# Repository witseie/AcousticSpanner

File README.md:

# DIY Acoustic Spanner

## Credits
* Ermes Toninelli, Mitchell A. Cox, Graham M. Gibson, Stuart D. Brown, Matthew P. Edgar, Andrew Forbes, Miles J. Padgett 
(Andrew.Forbes@wits.ac.za; Miles.Padgett@glasgow.ac.uk)

## Acknowledgements
* University of Glasgow, Scotland, United Kingdom
* University of the Witwatersrand, Johannesburg, South Africa
* EPSRC
* Centre for doctoral training in Intelligent Sensing and Measurment

## Introduction

Waves are ubiquitous in nature and we are all familiar with them: think water waves, light waves, sound waves, and so on. Everyone is familiar with the force that waves can impart on objects placed in their path. For example, a laser pointer shining on an object exerts a force on it, albeit a very small one. As it turns out, this force is directly proportional to the power of the wave and inversely proportional to its group velocity: that is, for the same power, a slower wave can exert a bigger force than a faster wave. Therefore, in the case of light waves the force is very small, as the speed of light is a very big number. Conversely, for the much slower sound waves (sound is approximately one million times slower than light) it is possible to exert a much bigger force, for an equal power expenditure.

In addition to linear momentum, both light and sound can carry orbital angular momentum (OAM). Whereas linear momentum allows one to ‘push’ objects along the direction of propagation, OAM can be used to rotate them! This form of momentum is different from the perhaps more familiar spin angular momentum, which gives rise to the phenomenon of polarisation, and it can be visualised, in the case of light, as each photon spinning on itself. When an OAM carrying field interacts with an object, it exerts a force both along the direction of propagation and around it: like the sort of force that is required to open a door, by both turning the door knob and by pushing the door.

Another example of the difference between spin angular momentum and orbital angular momentum is the Earth and Moon. The Earth rotates about it's own axis and thus has spin angular momentum. The Moon orbits around the Earth and thus has orbital angular momentum!

OAM arises from a phase structure within the field. Accordingly, many waves are used to create a certain field and the phase differences between these waves can be engineered by introducing delays, often referred to as a phased array. For example, if the waves are in phase with each other (i.e. without delays) the field can be visualised as a series of plane waves, for which the intensity of the waves is the same all over. If however, the phases are regularly changed from 0 to 2pi (one full cycle) in an azimuthal manner (going around the direction of propagation), then the field takes the form of a spiral. This is the type of field that gives rise to OAM.

In this work we use OAM carrying sound waves to build an acoustic spanner. An acoustic spanner allows to exert orbital angular momentum (OAM) on objects, causing them to rotate. Seeing this phenomenon in action is an excellent opportunity to think about the exchange of energy between sound waves and matter, and it is hence an important pedagogical tool. However, building an acoustic spanner able to spin macroscopic objects can require relatively expensive equipment and advanced technical skills. We show how to build a free-space acoustic spanner based on a 3D-printed sound-guiding structure and common electrical components. We show a video of our free-space acoustic spanner in action, in which a styrofoam packing peanut spins in a circular motion and changes direction according to the handedness of the OAM sound (see attached video).

## How do I build one?

1. You will need to get a PCB manufactured. Gerbers are provided which you can send through to your favourite manufacturer. We use Elecrow because they are cheap, fast and do a good job.
2. Accumulate all the compoments. A Bill Of Materials (BOM) is provided as a spreadsheet. The total cost is less than $100.
3. Learn to solder if you don't already know how (YouTube?). Solder all the components, carefully, to the PCB. 
4. Check your soldering and that each component is in the right place. Also check for solder bridges that shouldn't be there.
5. Burn the provided firmware to an Arduino Due using the Arduino IDE or Visual Studio Code.
6. Plug everything together and turn it on! You need to connect a 12V, 1A (or more) power supply to the top PCB for this to work.

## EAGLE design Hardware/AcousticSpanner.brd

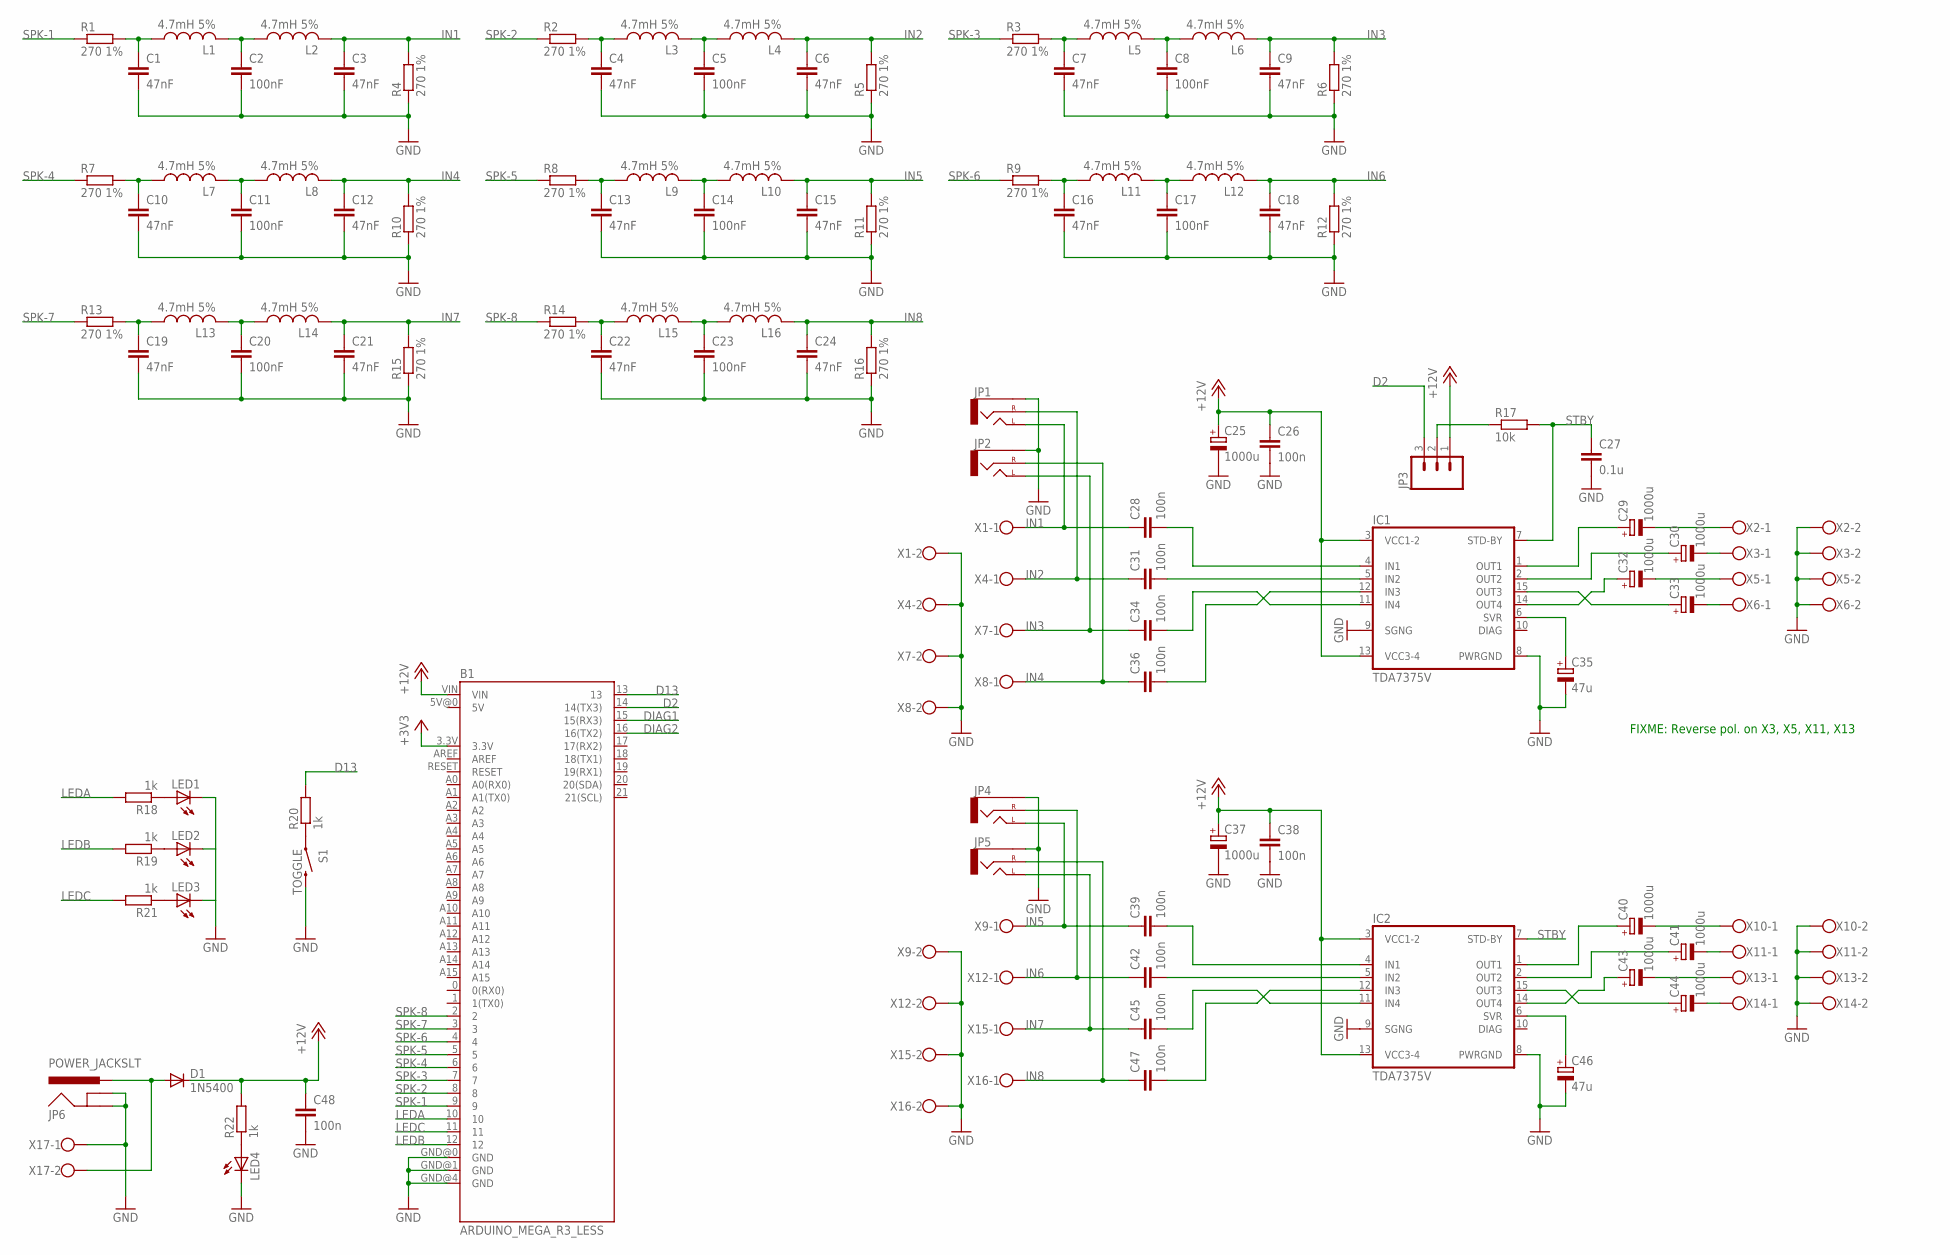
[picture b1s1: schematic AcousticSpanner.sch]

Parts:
B1: ARDUINO_MEGA_R3_LESS; ARDUINO_MEGA_LESS
C1, C3, C4, C6, C7, C9, C10, C12, C13, C15, C16, C18, C19, C21, C22, C24: 47nF; C025-025X050
C2, C5, C8, C11, C14, C17, C20, C23: 100nF; C025-025X050
C25, C29, C30, C32, C33, C37, C40, C41, C43, C44: 1000u; E5-10,5
C26, C28, C31, C34, C36, C38, C39, C42, C45, C47, C48: 100n; C025-025X050
C27: 0.1u; C025-025X050
C35, C46: 47u; E2,5-5
D1: 1N5400; DO201-15
IC1, IC2: TDA7375V; MULTIWATT-15V
JP1, JP2, JP4, JP5: AUDIO-JACKPTH; AUDIO-JACK
JP3: M03LOCK; 1X03_LOCK
JP6: POWER_JACKSLT; POWER_JACK_SLOT
L1, L2, L3, L4, L5, L6, L7, L8, L9, L10, L11, L12, L13, L14, L15, L16: 4.7mH 5%; 0207/2V
LED1, LED2, LED3, LED4: LED5MM
R1, R2, R3, R4, R5, R6, R7, R8, R9, R10, R11, R12, R13, R14, R15, R16: 270 1%; 0207/2V
R17: 10k; 0207/2V
R18, R19, R20, R21, R22: 1k; 0207/2V
S1: TOGGLE; TACTILE-PTH
X1, X2, X3, X4, X5, X6, X7, X8, X9, X10, X11, X12, X13, X14, X15, X16, X17: W237-102

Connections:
+3V3: B1.3.3V
+12V: B1.VIN, C25.+, C26.1, C37.+, C38.1, C48.1, D1.C, IC1.3 (VCC1-2), IC1.13 (VCC3-4), IC2.3 (VCC1-2), IC2.13 (VCC3-4), JP3.1, R22.2
D2: B1.14 (14(TX3)), JP3.3
D13: B1.13, R20.2
DIAG1: B1.15 (15(RX3))
DIAG2: B1.16 (16(TX2))
GND: B1.GND@0 (GND), B1.GND@1 (GND), B1.GND@4 (GND), C1.2, C2.2, C3.2, C4.2, C5.2, C6.2, C7.2, C8.2, C9.2, C10.2, C11.2, C12.2, C13.2, C14.2, C15.2, C16.2, C17.2, C18.2, C19.2, C20.2, C21.2, C22.2, C23.2, C24.2, C25.-, C26.2, C27.2, C35.-, C37.-, C38.2, C46.-, C48.2, IC1.8 (PWRGND), IC1.9 (SGNG), IC2.8 (PWRGND), IC2.9 (SGNG), JP1.SLEEVE, JP2.SLEEVE, JP4.SLEEVE, JP5.SLEEVE, JP6.GND@1 (GNDBREAK), JP6.GND@2 (GND), LED1.K (C), LED2.K (C), LED3.K (C), LED4.K (C), R4.1, R5.1, R6.1, R10.1, R11.1, R12.1, R15.1, R16.1, S1.3 (2), X1.2, X2.2, X3.2, X4.2, X5.2, X6.2, X7.2, X8.2, X9.2, X10.2, X11.2, X12.2, X13.2, X14.2, X15.2, X16.2, X17.1
IN1: C3.1, C28.1, JP1.TIP (LEFT), L2.2, R4.2, X1.1
IN2: C6.1, C31.1, JP1.RING (RIGHT), L4.2, R5.2, X4.1
IN3: C9.1, C34.1, JP2.TIP (LEFT), L6.2, R6.2, X7.1
IN4: C12.1, C36.1, JP2.RING (RIGHT), L8.2, R10.2, X8.1
IN5: C15.1, C39.1, JP4.TIP (LEFT), L10.2, R11.2, X9.1
IN6: C18.1, C42.1, JP4.RING (RIGHT), L12.2, R12.2, X12.1
IN7: C21.1, C45.1, JP5.TIP (LEFT), L14.2, R15.2, X15.1
IN8: C24.1, C47.1, JP5.RING (RIGHT), L16.2, R16.2, X16.1
LEDA: B1.10, R18.2
LEDB: B1.12, R19.2
LEDC: B1.11, R21.2
unnamed: C44.+, IC2.15 (OUT3)
unnamed: C32.+, IC1.14 (OUT4)
unnamed: C30.+, IC1.2 (OUT2)
unnamed: C29.+, IC1.1 (OUT1)
unnamed: C28.2, IC1.4 (IN1)
unnamed: C31.2, IC1.5 (IN2)
unnamed: C1.1, L1.1, R1.2
unnamed: C36.2, IC1.12 (IN3)
unnamed: C35.+, IC1.6 (SVR)
unnamed: JP3.2, R17.1
unnamed: C29.-, X2.1
unnamed: C30.-, X3.1
unnamed: C32.-, X5.1
unnamed: C33.-, X6.1
unnamed: LED4.A, R22.1
unnamed: C39.2, IC2.4 (IN1)
unnamed: C42.2, IC2.5 (IN2)
unnamed: C45.2, IC2.11 (IN4)
unnamed: C47.2, IC2.12 (IN3)
unnamed: C46.+, IC2.6 (SVR)
unnamed: C33.+, IC1.15 (OUT3)
unnamed: C43.+, IC2.14 (OUT4)
unnamed: C41.+, IC2.2 (OUT2)
unnamed: C40.+, IC2.1 (OUT1)
unnamed: C40.-, X10.1
unnamed: C41.-, X11.1
unnamed: C43.-, X13.1
unnamed: C44.-, X14.1
unnamed: LED1.A, R18.1
unnamed: LED2.A, R19.1
unnamed: R20.1, S1.1
unnamed: LED3.A, R21.1
unnamed: D1.A, JP6.PWR, X17.2
unnamed: C34.2, IC1.11 (IN4)
unnamed: C2.1, L1.2, L2.1
unnamed: C10.1, L7.1, R7.2
unnamed: C11.1, L7.2, L8.1
unnamed: C19.1, L13.1, R13.2
unnamed: C20.1, L13.2, L14.1
unnamed: C22.1, L15.1, R14.2
unnamed: C23.1, L15.2, L16.1
unnamed: C4.1, L3.1, R2.2
unnamed: C5.1, L3.2, L4.1
unnamed: C13.1, L9.1, R8.2
unnamed: C14.1, L9.2, L10.1
unnamed: C7.1, L5.1, R3.2
unnamed: C8.1, L5.2, L6.1
unnamed: C16.1, L11.1, R9.2
unnamed: C17.1, L11.2, L12.1
SPK-1: B1.9, R1.1
SPK-2: B1.8, R2.1
SPK-3: B1.7, R3.1
SPK-4: B1.6, R7.1
SPK-5: B1.5, R8.1
SPK-6: B1.4, R9.1
SPK-7: B1.3, R13.1
SPK-8: B1.2, R14.1
STBY: C27.1, IC1.7 (STD-BY), IC2.7 (STD-BY), R17.2

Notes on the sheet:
FIXME: Reverse pol. on X3, X5, X11, X13

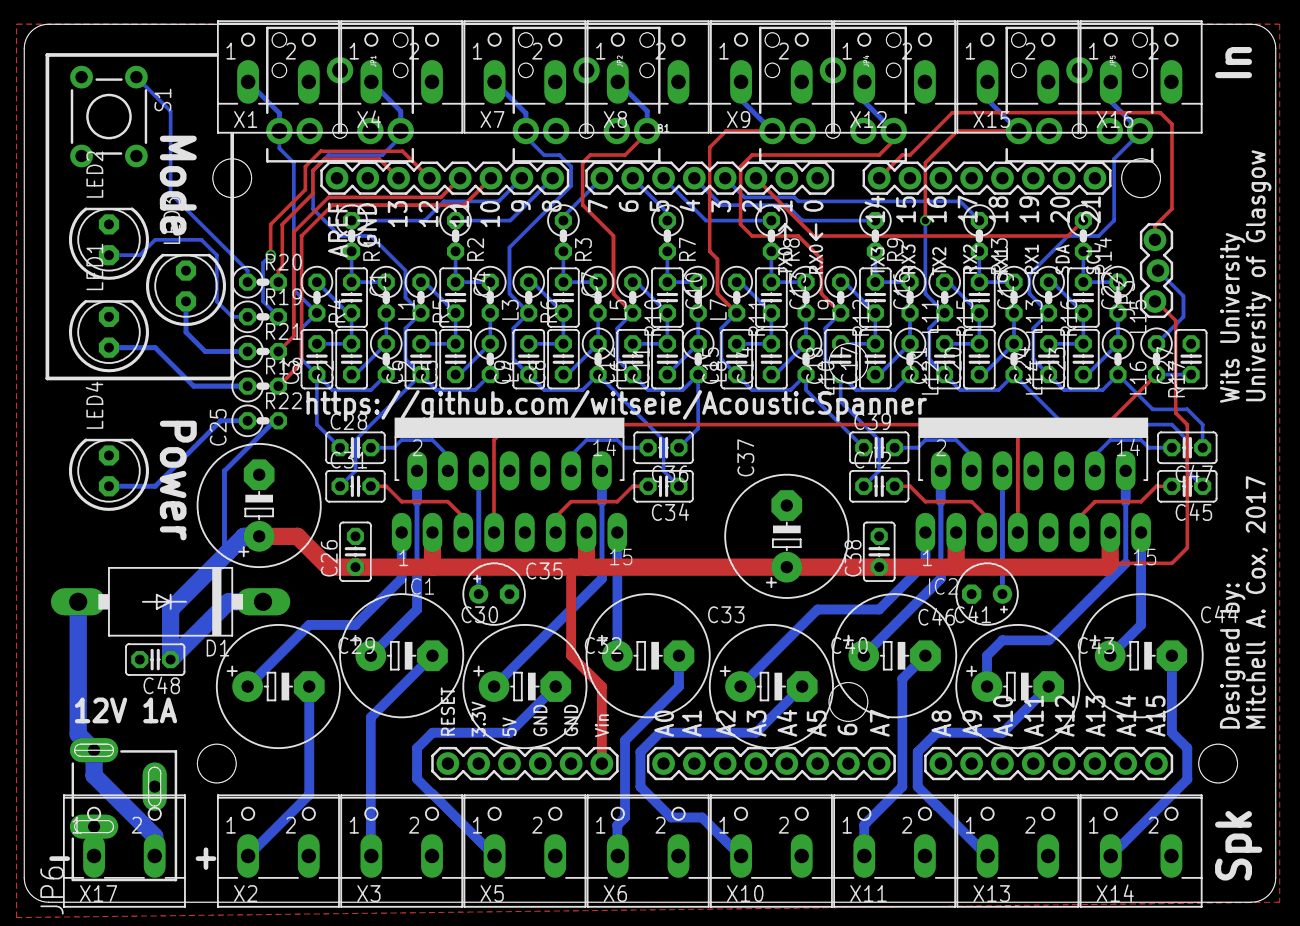
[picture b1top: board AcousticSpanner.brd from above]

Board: 2 copper layers, 103.2 x 72.4 mm, 118 parts (0 on the bottom side), 73 nets.

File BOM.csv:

Qty,Value,Device,Package,Parts,Description,,,,,,,,,,,,,,,,
4,Optional,AUDIO-JACKPTH,AUDIO-JACK,JP1, JP2, JP4, JP5,3.5mm Audio Jack,,,,,,,,,,,,,
4,,LED5MM,LED5MM,LED1, LED2, LED3, LED4,LED,,,,,,,,,,,,,
1,Pin Header,M03LOCK,1X03_LOCK,JP3,Header 3,,,,,,,,,,,,,,,,
17,Screw Terminal,W237-102,W237-102,X1, X2, X3, X4, X5, X6, X7, X8, X9, X10, X11, X12, X13, X14, X15, X16, X17,WAGO SCREW CLAMP
1,0.1u,C-EU025-025X050,C025-025X050,C27,CAPACITOR, European symbol,,,,,,,,,,,,,,,
10,1000u,CPOL-EUE5-10.5,E5-10,5,C25, C29, C30, C32, C33, C37, C40, C41, C43, C44,POLARIZED CAPACITOR, European symbol,,,,,
11,100n,C-EU025-025X050,C025-025X050,C26, C28, C31, C34, C36, C38, C39, C42, C45, C47, C48,CAPACITOR, European symbol,,,,,
8,100nF,C-EU025-025X050,C025-025X050,C2, C5, C8, C11, C14, C17, C20, C23,CAPACITOR, European symbol,,,,,,,,
1,10k,R-EU_0207/2V,0207/2V,R 17,RESISTOR, European symbol,,,,,,,,,,,,,,,
1,1N5400,1N5400,DO201-15,D1,DIODE,,,,,,,,,,,,,,,,
5,1k,R-EU_0207/2V,0207/2V,R 18,R 19,R 20,R 21,R 22,RESISTOR, European symbol,,,,,,,,,,,
16,270 1%,R-EU_0207/2V,0207/2V,R 1,R 2,R 3,R 4,R 5,R 6,R 7,R 8,R 9,R 10,R 11,R 12,R 13,R 14,R 15,R 16,RESISTOR, European symbol
16,4.7mH 5%,L-US0207/2V,0207/2V,L1, L2, L3, L4, L5, L6, L7, L8, L9, L10, L11, L12, L13, L14, L15, L16,INDUCTOR, American symbol
16,47nF,C-EU025-025X050,C025-025X050,C1, C3, C4, C6, C7, C9, C10, C12, C13, C15, C16, C18, C19, C21, C22, C24,CAPACITOR, European symbol
2,47u,CPOL-EUE2.5-5,E2,05-May,C35, C46,POLARIZED CAPACITOR, European symbol,,,,,,,,,,,,,
1,Arduino Due,Arduino Due,Arduino Due,B1,,,,,,,,,,,,,,,,,
1,POWER_JACKSLT,POWER_JACKSLT,POWER_JACK_SLOT,JP6,Power Jack,,,,,,,,,,,,,,,,
2,TDA7375V,TDA7375V,MULTIWATT-15V,IC1, IC2,,,,,,,,,,,,,,,,
1,TOGGLE,SWITCH-MOMENTARY-2PTH,TACTILE-PTH,S1,Various NO switches- pushbuttons, reed, etc,,,,,,,,,,,,,,

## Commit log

2017-10-31 Added initial README, firmware and hardware files.
2017-10-31 Added ISM CDT and EPSRC to the PCB
2017-10-31 Added a rough BOM
2017-11-01 Renamed to Acoustic Spanner
2017-11-13 Firmware updates
2017-11-13 added another example of OAM
2017-12-07 clean up and added bin file
2018-08-15 Add files via upload
    Added the source designs for Fusion360 (.f3z format) and the exported stereographic files (.stl format).
2018-08-15 Add files via upload
    Uploaded the videos of the 3d-printed acoustic spanner in action:
    1) graphiteFlakes.mov
    Rotational motion of macroscopic objects: rotation of graphite flakes floating on water. The circular motion of graphite flakes floating on the water surface qualitatively reveals the generated acous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
    2) packingPeanut.mov
    Rotational motion of macroscopic objects: rotation of a polystyrene packing peanut. A packing peanut is set into rotation by the intercepted OAM acoustic field.

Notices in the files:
parts and their libraries:
SparkFun-Boards: Licensing: Creative Commons ShareAlike 4.0 International - https://creativecommons.org/licenses/by-sa/4.0
